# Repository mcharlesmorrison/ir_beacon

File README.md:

# ir_beacon
IR beacon PCB for mid/long (up to ~18ft) range outdoor applications

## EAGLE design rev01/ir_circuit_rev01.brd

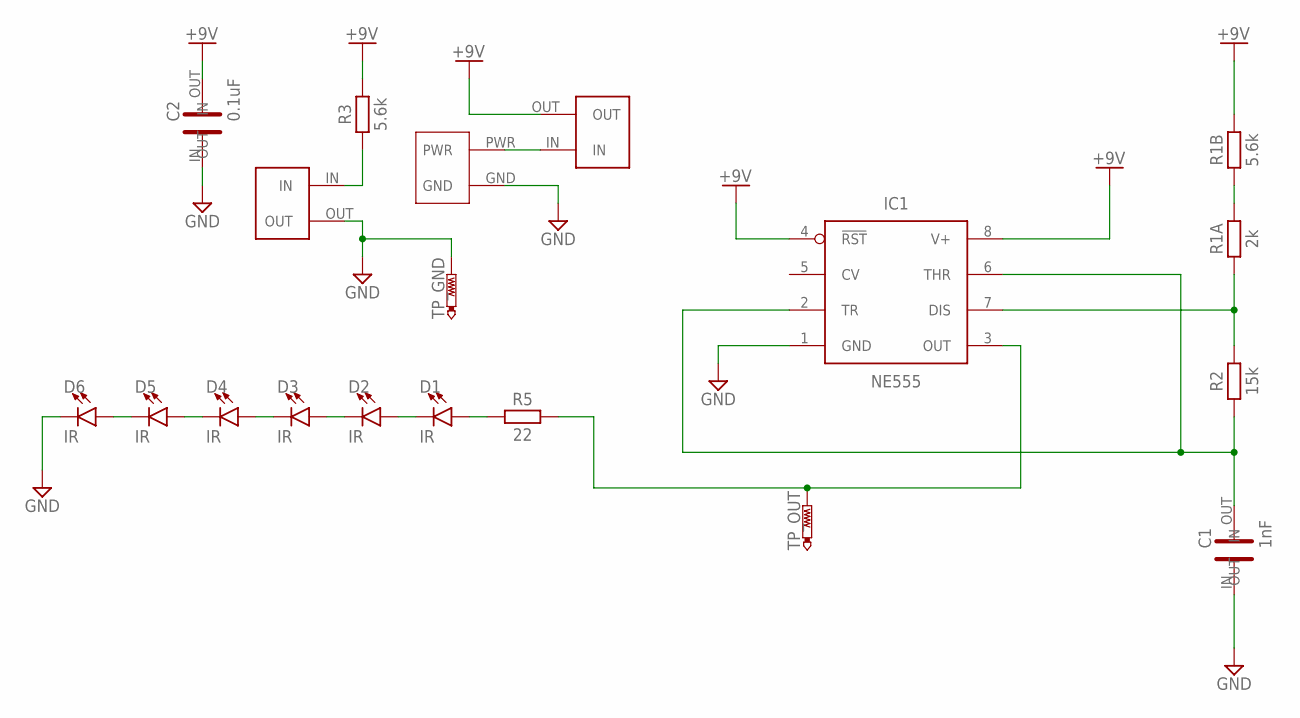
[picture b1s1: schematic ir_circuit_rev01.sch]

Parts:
BATT: JST_THRU_HOLE
C1: 1nF; THRU_HOLE_CAP
C2: 0.1uF; THRU_HOLE_CAP
D1, D2, D3, D4, D5, D6: IR; LED_5MM
IC1: NE555; DIP826W53P254L959H508Q8B
R1A: 2k; RESAD1176W63L850D250B
R1B, R3: 5.6k; RESAD1176W63L850D250B
R2: 15k; RESAD1176W63L850D250B
R5: 22; RESAD1176W63L850D250B
RED: LED; GEN_CONN
S1: GEN_CONN
TP_GND: PTR1B2,54; B2,54
TP_OUT: PTR1B2,54; B2,54

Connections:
+9V: C2.OUT, IC1.4 (!RST), IC1.8 (V+), R1B.2, R3.2, S1.OUT
GND: BATT.GND, C1.IN, C2.IN, D6.K (C), IC1.1 (GND), RED.OUT, TP_GND.TP
unnamed: C1.OUT, IC1.2 (TR), IC1.6 (THR), R2.1
unnamed: IC1.7 (DIS), R1A.1, R2.2
unnamed: D1.A, R5.1
unnamed: D1.K (C), D2.A
unnamed: D2.K (C), D3.A
unnamed: D3.K (C), D4.A
unnamed: D4.K (C), D5.A
unnamed: D5.K (C), D6.A
unnamed: R1A.2, R1B.1
unnamed: IC1.3 (OUT), R5.2, TP_OUT.TP
unnamed: BATT.PWR, S1.IN
unnamed: R3.1, RED.IN

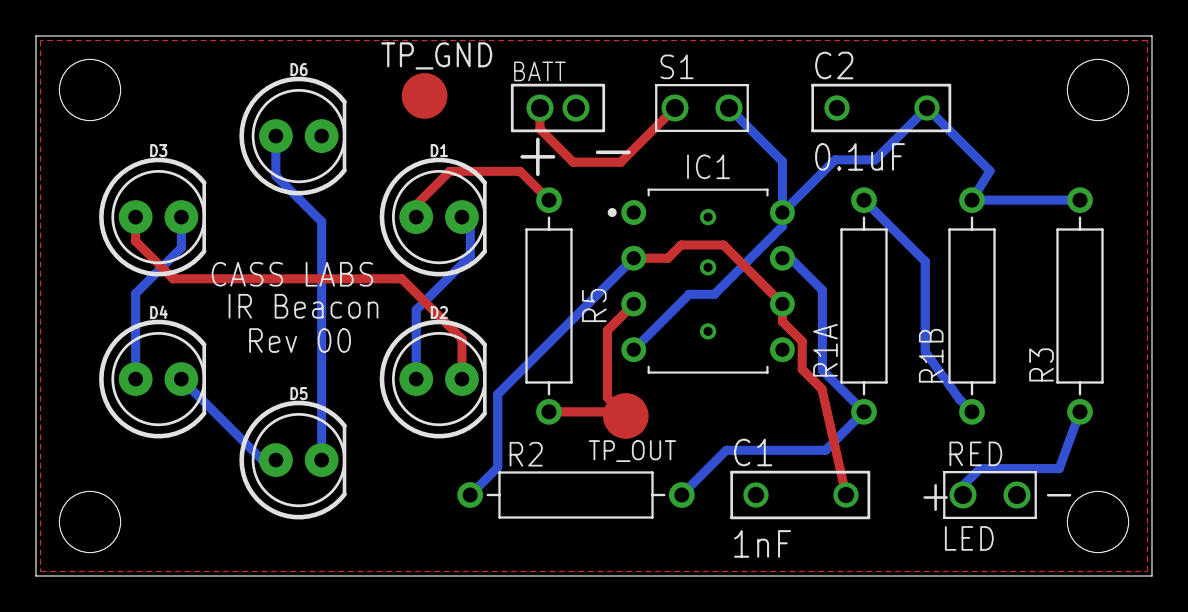
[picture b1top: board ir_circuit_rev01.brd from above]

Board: 2 copper layers, 62.0 x 30.0 mm, 19 parts (0 on the bottom side), 14 nets.

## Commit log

2024-07-30 rev00 of sch, brd, and cad
2024-07-30 add .gitignore
2024-08-08 Rev01 brd, sch, and stp. Updated resistor values and removed switch on board (it will be wired in line with battery for packaging reasons)
2024-08-15 Remove .DS_Store files

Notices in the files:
parts and their libraries:
SparkFun-LED: Licensing: Creative Commons ShareAlike 4.0 International - https://creativecommons.org/licenses/by-sa/4.0
